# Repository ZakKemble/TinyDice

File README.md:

Tiny Electronic Dice
====================

A tiny electronic dice.

http://blog.zakkemble.co.uk/a-tiny-electronic-dice/

---

Zak Kemble

contact@zakkemble.co.uk

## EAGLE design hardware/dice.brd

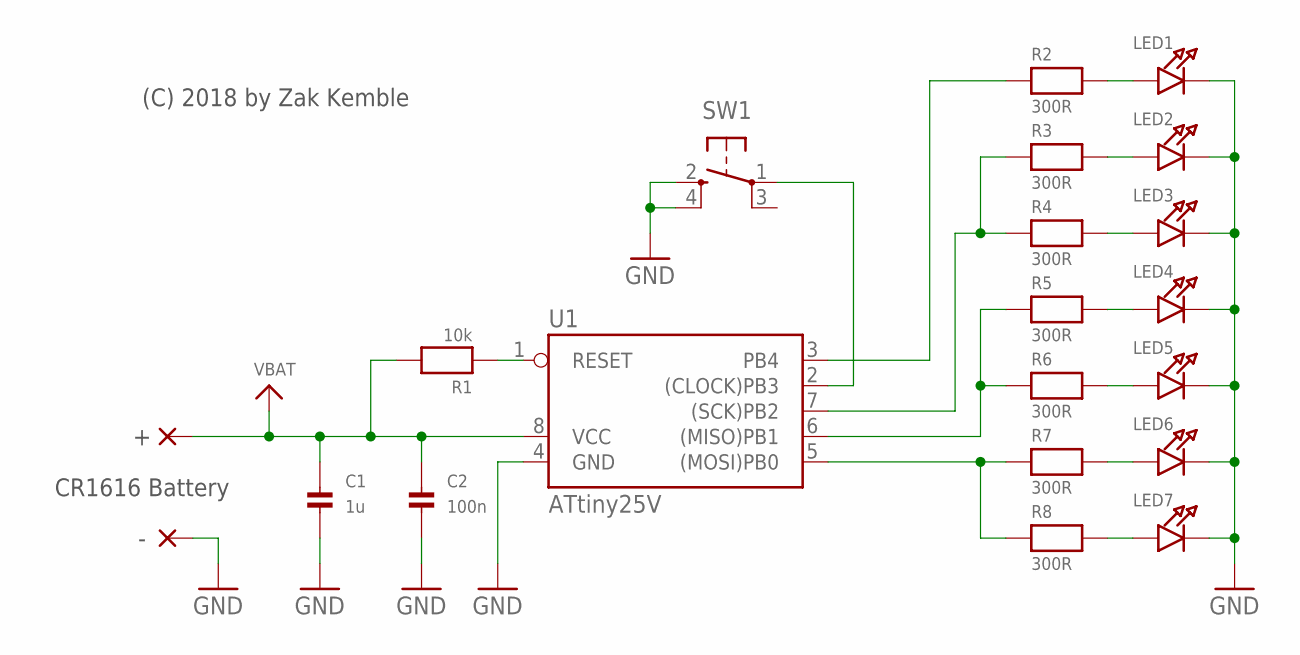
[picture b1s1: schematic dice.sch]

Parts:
C1: 1u; 0402
C2: 100n; 0402
LED1, LED2, LED3, LED4, LED5, LED6, LED7: LED0603_NOOUTLINE; CHIPLED_0603_NOOUTLINE
PAD1, PAD2: PADSMD-2X3; PAD-SMD-2X3
R1: 10k; 0402
R2, R3, R4, R5, R6, R7, R8: 300R; 0402
SW1: SPST_TACTRA; TACT_SMD2
U1: ATtiny25V; SOIC8_150MIL_SMPAD

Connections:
GND: C1.2, C2.2, LED1.C, LED2.C, LED3.C, LED4.C, LED5.C, LED6.C, LED7.C, PAD2.1, SW1.2 (S), SW1.4 (S1), U1.4 (GND)
unnamed: R1.1, U1.1 (RESET)
unnamed: R3.1, R4.1, U1.7 ((SCK)PB2)
unnamed: R7.1, R8.1, U1.5 ((MOSI)PB0)
unnamed: R5.1, R6.1, U1.6 ((MISO)PB1)
unnamed: SW1.1, U1.2 ((CLOCK)PB3)
unnamed: LED6.A, R7.2
unnamed: LED7.A, R8.2
unnamed: R2.1, U1.3 (PB4)
unnamed: LED4.A, R5.2
unnamed: LED5.A, R6.2
unnamed: LED1.A, R2.2
unnamed: LED3.A, R4.2
unnamed: LED2.A, R3.2
VBAT: C1.1, C2.1, PAD1.1, R1.2, U1.8 (VCC)

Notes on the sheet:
CR1616 Battery
(C) 2018 by Zak Kemble

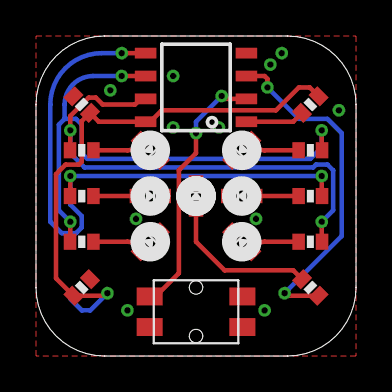
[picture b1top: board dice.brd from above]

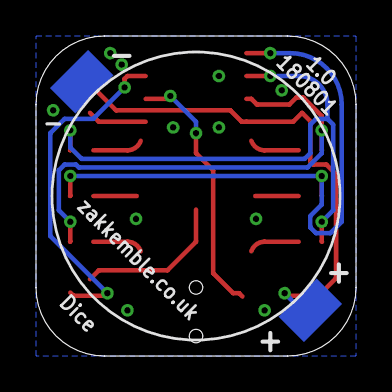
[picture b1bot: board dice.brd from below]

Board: 2 copper layers, 17.8 x 17.8 mm, 21 parts (2 on the bottom side), 15 nets.

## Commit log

2018-09-02 Add copyright notice for the XORShift algo

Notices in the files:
parts and their libraries:
microbuilder: This work is placed in the public domain, and may be freely used for commercial and non-commercial work with the following conditions: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
